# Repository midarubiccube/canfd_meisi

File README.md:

# 基板概要

この名刺はPCとつなぐだけでCANFDができるという最高で実用性マシマシの名刺となっています。
特徴として
+ SLCANでserialを経由しCANが可能
+ CANFD2ch搭載
+ CANFDをLANケーブルに変換
+ 終端抵抗
+ LANケーブルでPoE給電（12V）が可能。
+ インジケータ付き

といった感じです。

# 実装の仕方

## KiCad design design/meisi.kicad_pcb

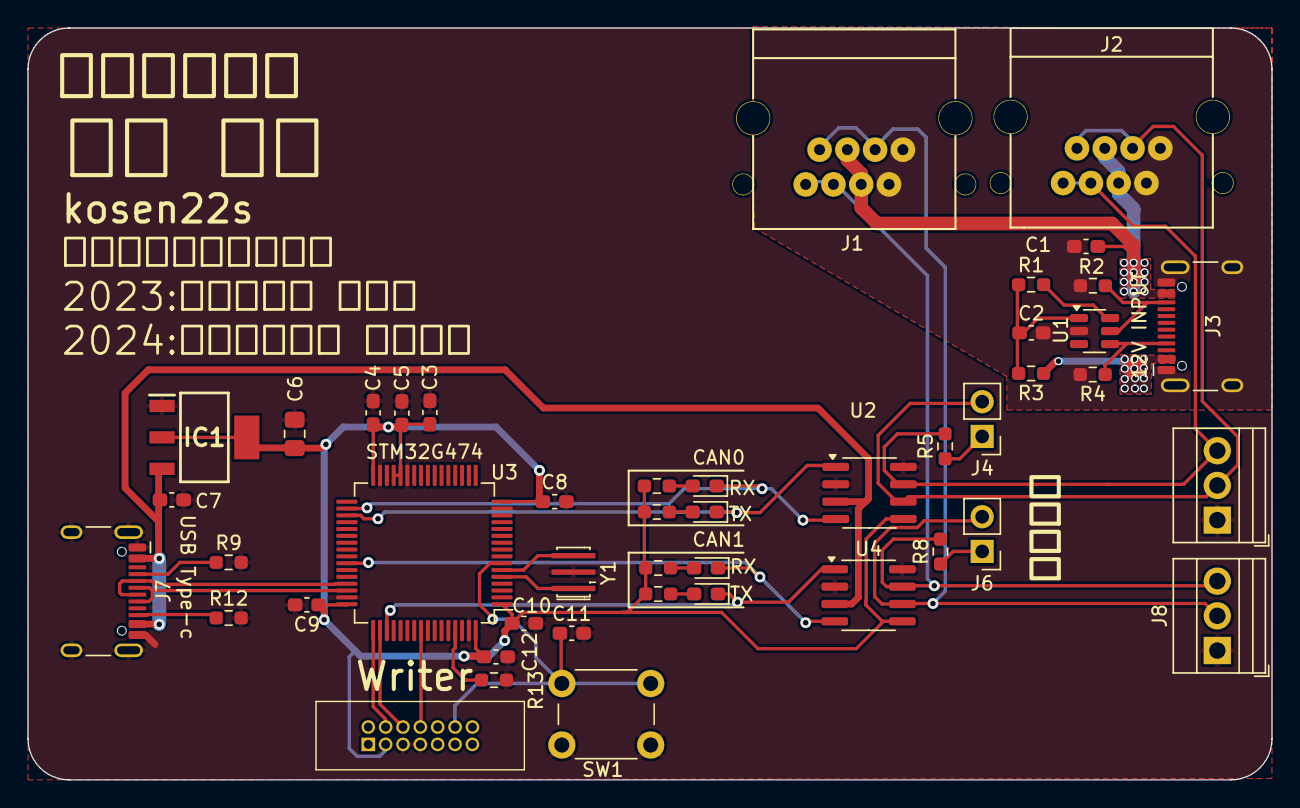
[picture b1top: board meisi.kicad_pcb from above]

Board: 2 copper layers, 91.0 x 55.0 mm, 45 parts (0 on the bottom side), 34 nets.

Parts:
C1, C7: 0.1μF; C_0603_1608Metric_Pad1.08x0.95mm_HandSolder
C2: 1μF; C_0603_1608Metric_Pad1.08x0.95mm_HandSolder
C3, C4, C5, C8, C9, C10, C11, C12: C; C_0603_1608Metric_Pad1.08x0.95mm_HandSolder
C6: 10µF; C_0805_2012Metric_Pad1.18x1.45mm_HandSolder
D1, D2, D3, D4: LED; LED_0603_1608Metric_Pad1.05x0.95mm_HandSolder
IC1: AZ1117CH-3.3TRG1; SOT230P700X180-4N
J1, J2: RJ45; 7810-8P8C
J3, J7: USB_C_Receptacle_USB2.0; USB_C_Receptacle_HCTL_HC-TYPE-C-16P-01A
J4, J6: Conn_01x02_Pin; PinHeader_1x02_P2.54mm_Vertical
J5, J8: Screw_Terminal_01x03; TerminalBlock_Xinya_XY308-2.54-3P_1x03_P2.54mm_Horizontal
J9: Conn_02x07_Odd_Even; connector
R1: 47kΩ; R_0603_1608Metric_Pad0.98x0.95mm_HandSolder
R2, R4: 5.1kΩ; R_0603_1608Metric_Pad0.98x0.95mm_HandSolder
R3: 1kΩ; R_0603_1608Metric_Pad0.98x0.95mm_HandSolder
R5, R8: 120Ω; R_0603_1608Metric_Pad0.98x0.95mm_HandSolder
R6, R7, R10, R11: 1k; R_0603_1608Metric_Pad0.98x0.95mm_HandSolder
R9, R12: 5.1k; R_0603_1608Metric_Pad0.98x0.95mm_HandSolder
R13: 10k; R_0603_1608Metric_Pad0.98x0.95mm_HandSolder
SW1: SW_Push; SW_PUSH_6mm_H5mm
U1: CH221K; SOT-23-6
U2, U4: MCP2562-E-SN; SOIC-8_3.9x4.9mm_P1.27mm
U3: STM32G474; LQFP-64_10x10mm_P0.5mm
Y1: Crystal_GND2; Resonator_SMD_Murata_CSTxExxV-3Pin_3.0x1.1mm_HandSoldering

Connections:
+3.3V: C3.1, C4.1, C5.1, C6.1, C8.1, C9.1, C10.1, C12.1, IC1.2 (OUTPUT), IC1.4 (VOUT), J9.3, R6.1, R7.1, R10.1, R11.1, U2.5 (Vio), U3.1 (VBAT), U3.16 (VDD), U3.28 (VREF+), U3.29 (VDDA), U3.32 (VDD), U3.48 (VDD), U3.64 (VDD), U4.5 (Vio)
+5V: C7.1, IC1.3 (INPUT), J7.A4 (VBUS), J7.A9 (VBUS), J7.B4 (VBUS), J7.B9 (VBUS), U2.3 (VDD), U4.3 (VDD)
+12V: C1.1, J1.4, J1.5, J2.4, J2.5, J3.A4 (VBUS), J3.A9 (VBUS), J3.B4 (VBUS), J3.B9 (VBUS), R3.1
/CANFD1/CANH: J1.1, J1.3, J8.3, R8.2, U4.7 (CANH)
/CANFD1/CANL: J1.2, J1.6, J6.2, J8.2, U4.6 (CANL)
/CANFD1/CANRX: D3.1 (K), U3.42 (PA8), U4.4 (RXD)
/CANFD1/CANTX: D4.1 (K), U3.51 (PA15), U4.1 (TXD)
/CANFD/CANH: J2.1, J2.3, J5.3, R5.2, U2.7 (CANH)
/CANFD/CANL: J2.2, J2.6, J4.2, J5.2, U2.6 (CANL)
/CANFD/CANRX: D1.1 (K), U2.4 (RXD), U3.34 (PB12)
/CANFD/CANTX: D2.1 (K), U2.1 (TXD), U3.35 (PB13)
/MCU/USB_DM: J7.A7 (D-), J7.B7 (D-), U3.45 (PA11)
/MCU/USB_DP: J7.A6 (D+), J7.B6 (D+), U3.46 (PA12)
GND: C3.2, C4.2, C5.2, C6.2, C7.2, C8.2, C9.2, C10.2, C11.2, C12.2, IC1.1 (ADJ/GND), J5.1, J7.A1 (GND), J7.A12 (GND), J7.B1 (GND), J7.B12 (GND), J7.S1 (SHIELD), J8.1, J9.5, J9.7, R9.2, R12.2, R13.2, SW1.1, U2.2 (VSS), U2.8 (STBY), U3.15 (VSS), U3.27 (VSSA), U3.31 (VSS), U3.47 (VSS), U3.63 (VSS), U4.2 (VSS), U4.8 (STBY), Y1.2
GND2: C1.2, C2.2, J1.7, J1.8, J2.7, J2.8, J3.A1 (GND), J3.A12 (GND), J3.B1 (GND), J3.B12 (GND), J3.S1 (SHIELD), R2.2, R4.2, U1.2 (GND)
NRST: C11.1, J9.12, SW1.2, U3.7 (PG10)
unnamed: D1.2 (A), R6.2
unnamed: D2.2 (A), R7.2
unnamed: D3.2 (A), R10.2
unnamed: D4.2 (A), R11.2
unnamed: J3.A5 (CC1), R4.1, U1.4 (CC1)
unnamed: J3.B5 (CC2), R2.1, U1.5 (CC2)
unnamed: J4.1, R5.1
unnamed: J6.1, R8.1
unnamed: J7.A5 (CC1), R9.1
unnamed: J7.B5 (CC2), R12.1
unnamed: R1.2, U1.6 (CFG)
unnamed: C2.1, R1.1, R3.2, U1.1 (VDD)
unnamed: R13.1, U3.61 (PB8)
unnamed: U3.5 (PF0), Y1.1
unnamed: U3.6 (PF1), Y1.3
T_SWCLK: J9.6, U3.50 (PA14)
T_SWDIO: J9.4, U3.49 (PA13)
T_SWO: J9.8, U3.56 (PB3)

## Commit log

2024-12-13 README.を追加
